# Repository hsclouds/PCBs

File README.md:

# PCBs

Notes: 
1. Only uploading PCB design projects done in-house for Softgalaxy Technologies Inc or ones updated having open hardware, GNU style licenses.
2. Each directory contains all the relevant design files, libraries, documentation for the project.
3. Giving a brief overview of each PCB design project.
4. I have done PCB design projects using Altium, KiCAD, Eagle, Protel, Cadence Allegro, Redac

AMD-Spartan7-KiCAD: A breakout board using Xilinx Spartan7.

FPGAs-KiCAD-Ard_RPi_BB: One PCB project having numerous FPGA vendors chipsets for evaluation to be manufactured as one board having multiple breakout boards.

Eagle: This directory contains the PCB projects done using Eagle software.

Altium: This directory contains the PCB projects done using the Altium designer software.

Protel: This directory contains the PCB projects done using the Protel 99 before re-branded as Altium.

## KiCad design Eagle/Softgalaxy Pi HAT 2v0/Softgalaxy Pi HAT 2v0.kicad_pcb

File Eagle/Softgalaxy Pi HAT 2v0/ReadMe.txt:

This PCB project is done to add CAN bus functionality to Raspberry Pi.

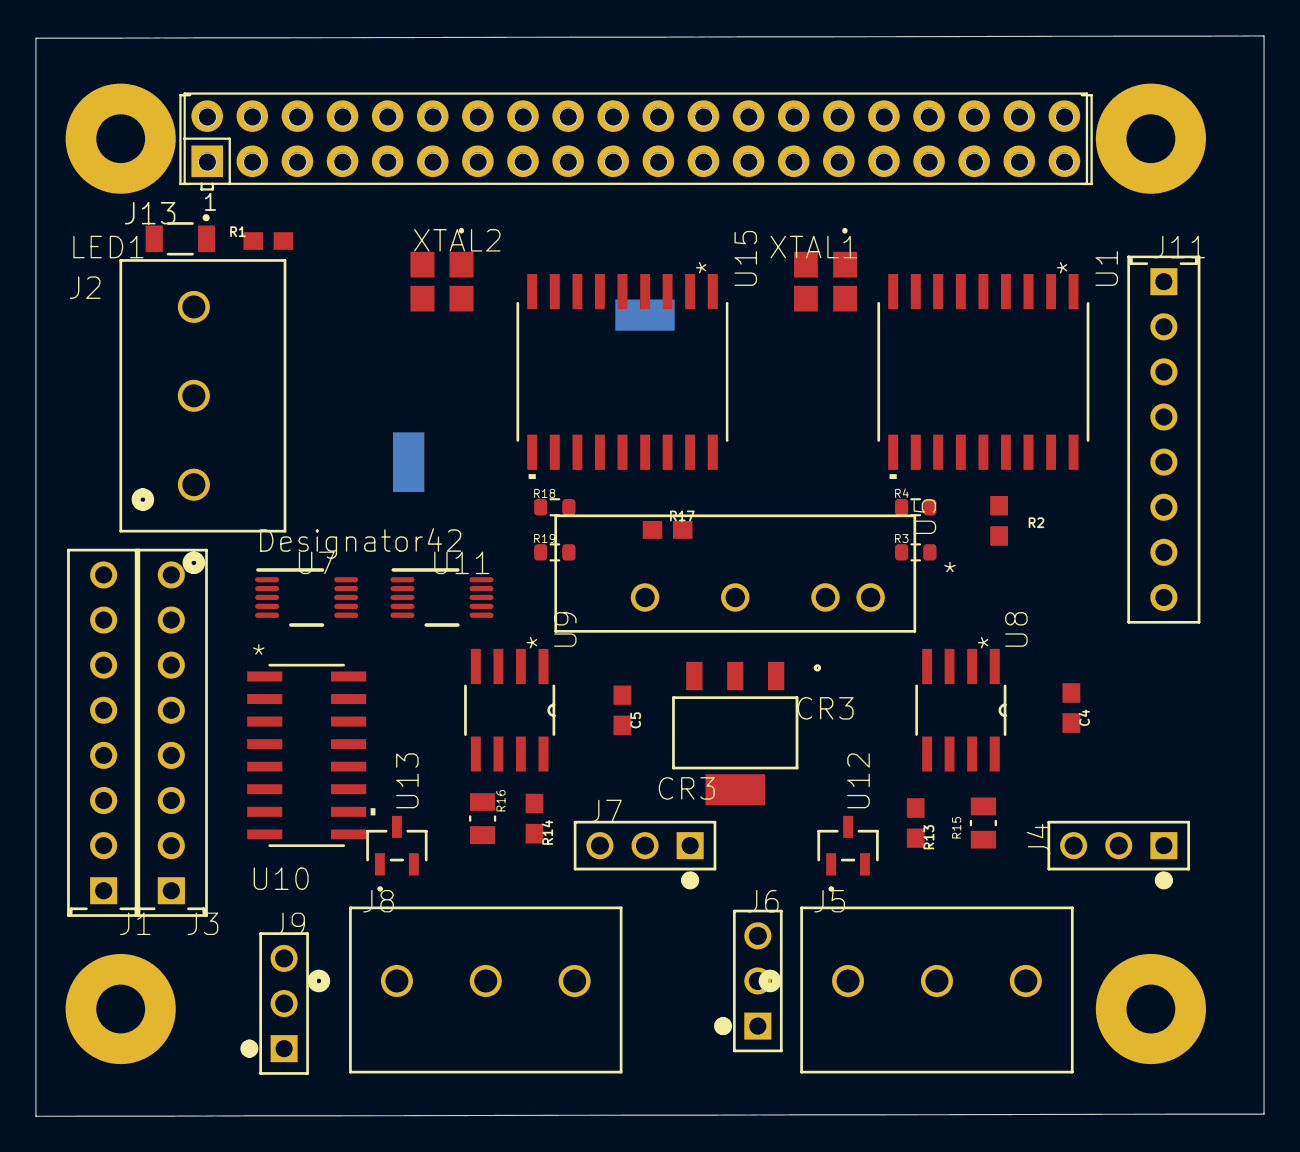
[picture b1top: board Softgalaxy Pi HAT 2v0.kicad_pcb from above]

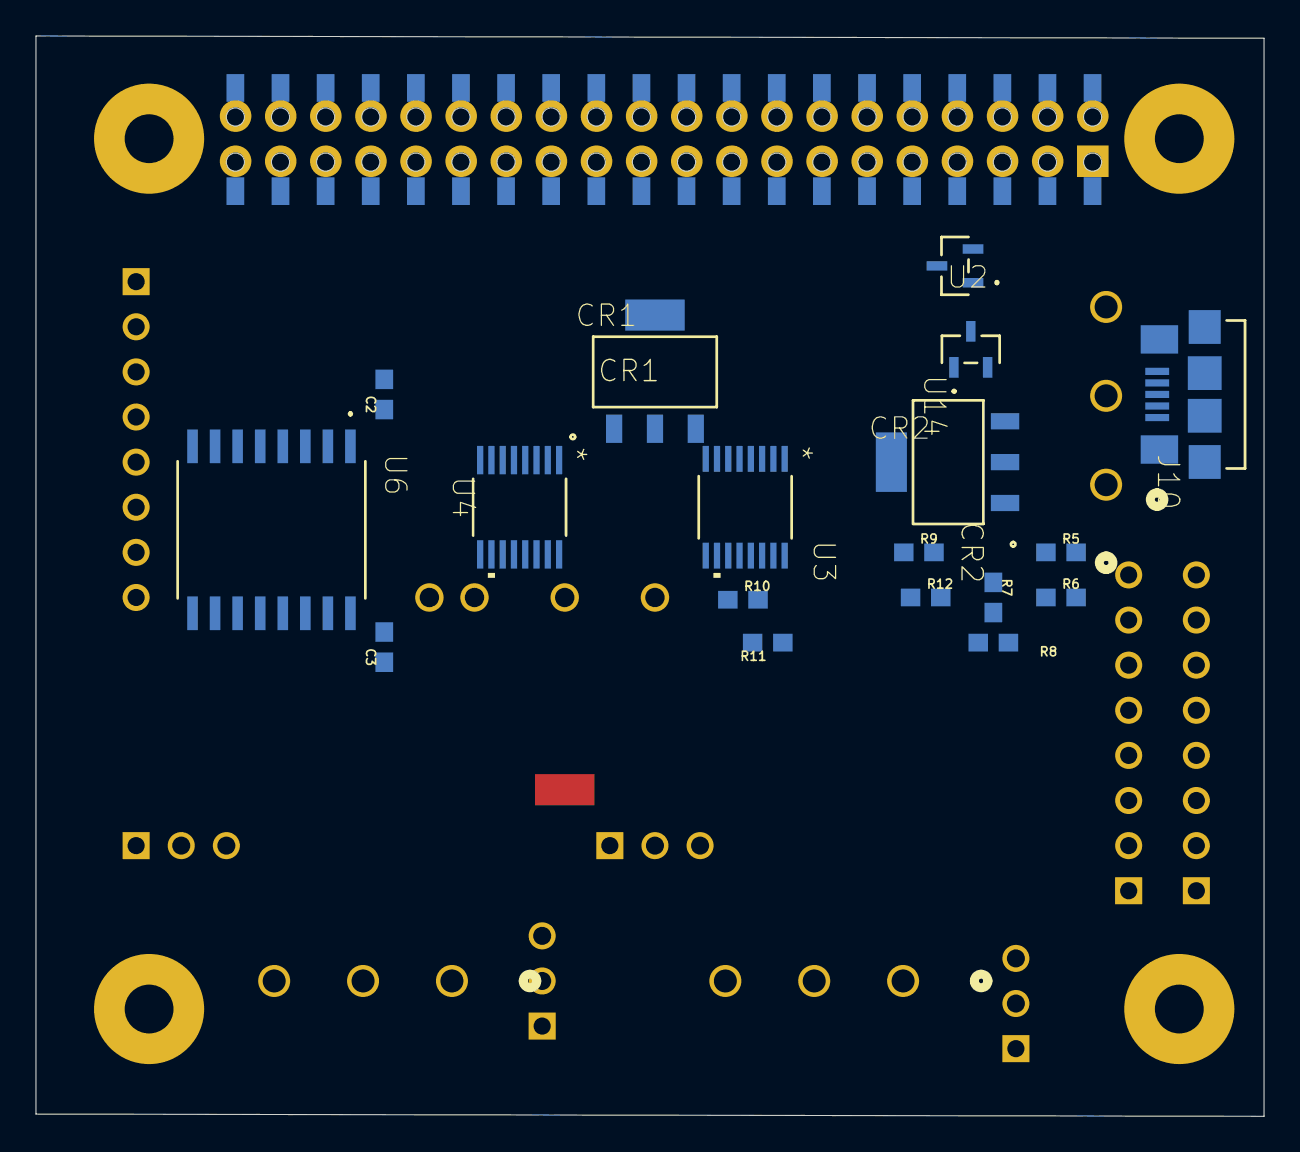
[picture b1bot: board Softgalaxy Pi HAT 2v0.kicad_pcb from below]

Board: 2 copper layers, 69.1 x 60.8 mm, 57 parts (18 on the bottom side), 80 nets, no tracks yet.

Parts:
C2, C3, C4, C5: 10nF; 0603
CR1, CR3: LD1117S33CTR; SOT-223_STM
CR2: LD1117S50CTR; SOT-223_STM
J1, J3, J11: 828214-8; CON8_1X8_P100UM_HDR
J2, J5, J8: 1935174; CONN_1935174_PXC
J4, J6, J7, J9: 77311-101-03LF; 77311-101-03LF_AMP
J10: 10118192-0002LF; CONN_10118192-0002LF_AMP
J13: NPTC202KFMS-RC; SULLINS_NPTC202KFMS-RC
LED1: 15-21SURC/S530-A3/TR8; LED_15-21SURC_S530-A3_TR8_EVE
R1: 4.7k; 0603
R2, R5, R6, R7, R8, R9, R10, R11, R12, R17: 10k; 0603
R3, R4, R18, R19: RC0603JR-070RL; RES_0603
R13, R14: 1k; 0603
R15, R16: CRGCQ0805F120R; RESC2012X65N
U1, U15: MCP2515T-I/SO; SOIC18-W_MC_MCH
U2, U14: PMEG2005CT,215; SOT_05CT215_NEX
U3: MAX14850AEE+; 21-0055H_16_MXM
U4: MAX14431CAEE+; 21-0055Q_E16MS+1F_MXM
U5: B0505LS-1WR2; B0505LS-1WR2_MNS
U6: SI8642ED-B-IS; SOIC-16W_SIL
U7: ADS1115IDGST; DGS0010A_N
U8, U9: SN65HVD230QDG4Q1; D8
U10: MCP3008T-I/SL; SOIC16-N_MC_MCH
U11: ADS1015IDGSR; DGS0010A_N
U12, U13: SM24CANB-02HTG; SOT23-3_SM24CANB-02HTG_LTF
X1: RASPI_BOARD_B+#_FP; RASPI_BOARD_B+_FULL_PAD
XTAL1, XTAL2: TSX-3225_16.0000MF18X-AC6; TSX-3225_16.0000MF18X-AC6_EPS

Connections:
+3V3: C2.1, CR1.2, R2.1, R17.1, U1.18, U3.1, U4.1, U6.1, U15.18
+5V: J13.2, J13.4, R1.2, U14.1, X1.2, X1.4
CAN0_INT: R3.2, R4.2, U1.12
CAN1_INT: R18.2, R19.2, U15.12
GND: C2.2, CR1.1, CR2.1, J2.3, J10.5, J10.6, J10.7, J10.8, J10.9, J10.10, J10.11, J11.1, J13.6, J13.9, J13.14, J13.20, J13.25, J13.30, J13.34, J13.39, LED1.1, U1.9, U3.8, U4.8, U5.2, U6.2, U6.8, U15.9, X1.6, X1.9, X1.14, X1.20, X1.25, X1.30, X1.34, X1.39, XTAL1.2, XTAL1.4, XTAL2.2, XTAL2.4
GNDA: C4.2, C5.2, CR3.1, J1.1, J1.2, J1.3, J1.4, J1.5, J1.6, J1.7, J1.8, J5.3, J6.3, J8.3, J9.3, R12.2, R13.2, R14.2, U3.9, U4.9, U5.4, U6.9, U7.3, U8.2, U9.2, U10.9, U10.14, U11.3, U12.3, U13.3
unnamed: U1.7, XTAL1.1
unnamed: U1.8, XTAL1.3
unnamed: J10.1, U14.2
unnamed: U2.1, U14.3
unnamed: R2.2, U1.17
unnamed: LED1.2, R1.1
unnamed: C3.2, U6.16
unnamed: J4.2, R15.2
unnamed: R13.1, U8.8
unnamed: J5.1, J6.1, R15.1, U8.7, U12.2
unnamed: J4.3, J5.2, J6.2, U8.6, U12.1
unnamed: R14.1, U9.8
unnamed: J8.1, J9.1, R16.1, U9.7, U13.2
unnamed: J7.3, J8.2, J9.2, U9.6, U13.1
unnamed: J7.2, R16.2
unnamed: U4.11, U10.12
unnamed: U4.13, U10.11
unnamed: U4.12, U10.10
unnamed: CR2.3, U2.3
unnamed: R8.1, R10.1, U3.15, U7.10, U11.10
unnamed: R7.1, R11.1, U3.11, U7.9, U11.9
unnamed: R12.1, U11.1
unnamed: J2.1, U2.2
unnamed: J3.1, U10.8
unnamed: R9.2, U11.2
unnamed: J3.2, U10.7
unnamed: J3.3, U10.6
unnamed: R6.1, U7.1
unnamed: R5.1, U7.2
unnamed: J3.4, U10.5
unnamed: J3.5, U7.7, U10.4, U11.7
unnamed: J3.6, U7.6, U10.3, U11.6
unnamed: J3.7, U7.5, U10.2, U11.5
unnamed: J3.8, U7.4, U10.1, U11.4
unnamed: U4.14, U10.13
unnamed: CR3.3, U5.6
unnamed: R17.2, U15.17
unnamed: U15.8, XTAL2.3
unnamed: U15.7, XTAL2.1
unnamed: U6.4, U15.1
PI_GPIO04: J13.7, X1.7
PI_GPIO05: J13.29, X1.29
PI_GPIO06: J13.31, X1.31
PI_GPIO12: J13.32, X1.32
PI_GPIO13: J13.33, X1.33
PI_GPIO16: J13.36, X1.36
PI_GPIO17: J13.11, X1.11
PI_GPIO18: J13.12, X1.12
PI_GPIO19: J13.35, X1.35
PI_GPIO20: J13.38, X1.38
PI_GPIO21: J13.40, X1.40
PI_GPIO22: J13.15, R4.1, X1.15
PI_GPIO23: J13.16, R3.1, X1.16
PI_GPIO24: J13.18, R19.1, X1.18
PI_GPIO25: J13.22, R18.1, X1.22
PI_GPIO26: J13.37, X1.37
PI_GPIO27: J13.13, X1.13
PI_RXD: J13.10, X1.10
PI_SC: J13.28, X1.28
PI_SCL: J13.5, X1.5
PI_SD: J13.27, X1.27
PI_SDA: J13.3, X1.3
PI_TXD: J13.8, X1.8
RXD0: U1.2, U6.5
RXD1: U6.6, U15.2
SPI0_CE0: J11.5, J13.24, U1.16, X1.24
SPI0_CE1: J11.4, J13.26, U15.16, X1.26
SPI0_MISO: J11.7, J13.21, U1.15, U15.15, X1.21
SPI0_MOSI: J11.8, J13.19, U1.14, U15.14, X1.19
SPI0_SCK: J11.6, J13.23, U1.13, U15.13, X1.23
TXD0: U1.1, U6.3
V+: C3.1, C4.1, C5.1, CR3.2, R5.2, R6.2, R7.2, R8.2, R9.1, R10.2, R11.2, U3.16, U4.16, U7.8, U8.3, U9.3, U10.15, U10.16, U11.8
VCC: CR1.3, CR2.2, U5.1
VDD: J13.1, J13.17, X1.1, X1.17

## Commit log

2023-05-11 Breakout boards using FPGAs from different vendors on a PCB which can be a hat on Raspberry Pi, Arduino or Beaglebone.
2023-05-11 Spartan 7 breakout board PCB project
